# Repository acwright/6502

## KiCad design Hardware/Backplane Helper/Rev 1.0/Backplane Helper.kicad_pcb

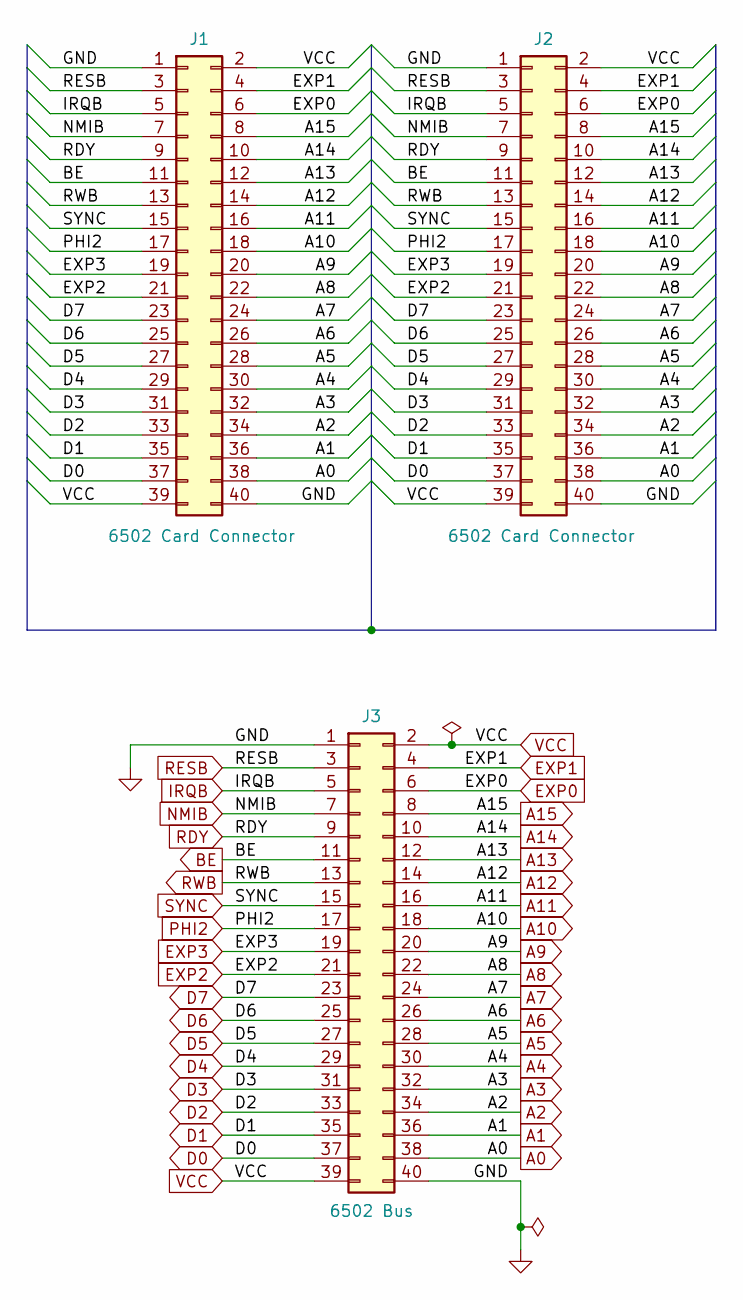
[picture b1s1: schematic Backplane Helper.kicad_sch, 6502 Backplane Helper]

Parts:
J1, J2: 6502 Card Connector; RHDR40W82P485X254_2X20_5740X93; Mouser 571-5-5530843-4
J3: 6502 Bus; 6502 Bus Connector; Digikey 732-5401-ND

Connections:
A0: J1.38, J2.38, J3.38
A1: J1.36, J2.36, J3.36
A2: J1.34, J2.34, J3.34
A3: J1.32, J2.32, J3.32
A4: J1.30, J2.30, J3.30
A5: J1.28, J2.28, J3.28
A6: J1.26, J2.26, J3.26
A7: J1.24, J2.24, J3.24
A8: J1.22, J2.22, J3.22
A9: J1.20, J2.20, J3.20
A10: J1.18, J2.18, J3.18
A11: J1.16, J2.16, J3.16
A12: J1.14, J2.14, J3.14
A13: J1.12, J2.12, J3.12
A14: J1.10, J2.10, J3.10
A15: J1.8, J2.8, J3.8
BE: J1.11, J2.11, J3.11
D0: J1.37, J2.37, J3.37
D1: J1.35, J2.35, J3.35
D2: J1.33, J2.33, J3.33
D3: J1.31, J2.31, J3.31
D4: J1.29, J2.29, J3.29
D5: J1.27, J2.27, J3.27
D6: J1.25, J2.25, J3.25
D7: J1.23, J2.23, J3.23
EXP0: J1.6, J2.6, J3.6
EXP1: J1.4, J2.4, J3.4
EXP2: J1.21, J2.21, J3.21
EXP3: J1.19, J2.19, J3.19
GND: J1.1, J1.40, J2.1, J2.40, J3.1, J3.40
IRQB: J1.5, J2.5, J3.5
NMIB: J1.7, J2.7, J3.7
PHI2: J1.17, J2.17, J3.17
RDY: J1.9, J2.9, J3.9
RESB: J1.3, J2.3, J3.3
RWB: J1.13, J2.13, J3.13
SYNC: J1.15, J2.15, J3.15
VCC: J1.2, J1.39, J2.2, J2.39, J3.2, J3.39

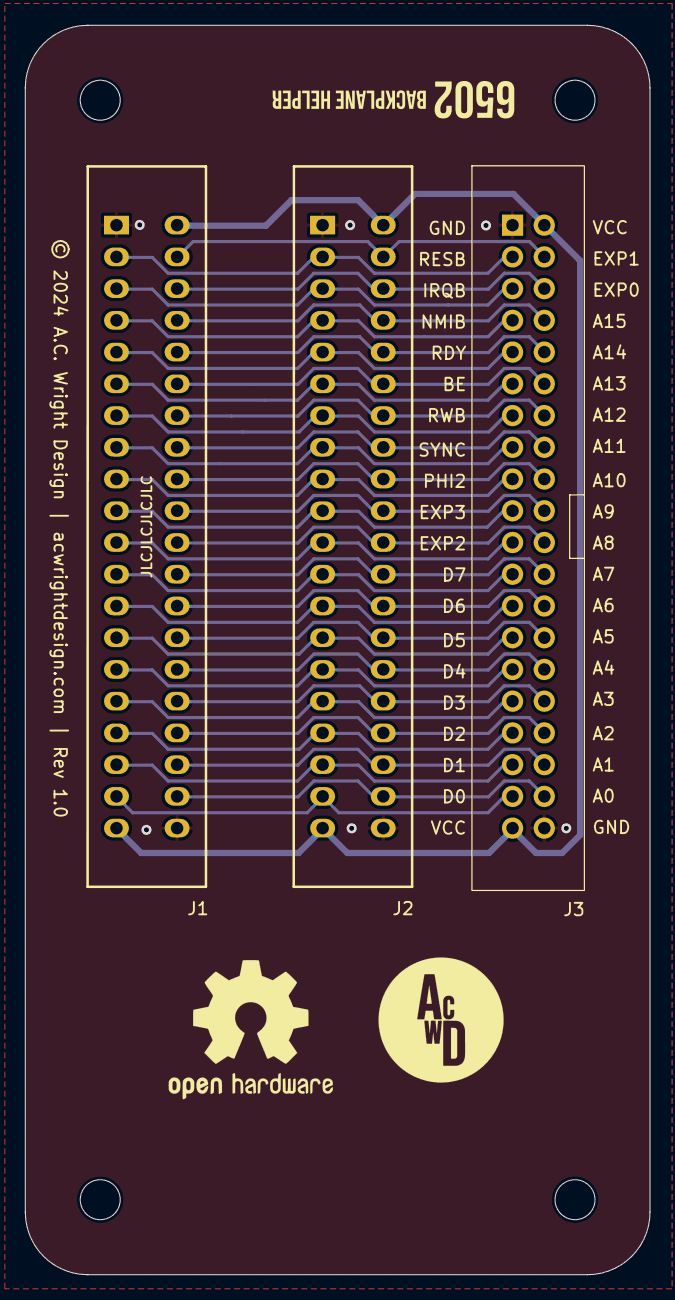
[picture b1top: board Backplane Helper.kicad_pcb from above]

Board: 2 copper layers, 50.0 x 100.0 mm, 7 parts (0 on the bottom side), 38 nets.

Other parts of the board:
H1, H2, H3, H4: MountingHole; MountingHole_3.2mm_M3

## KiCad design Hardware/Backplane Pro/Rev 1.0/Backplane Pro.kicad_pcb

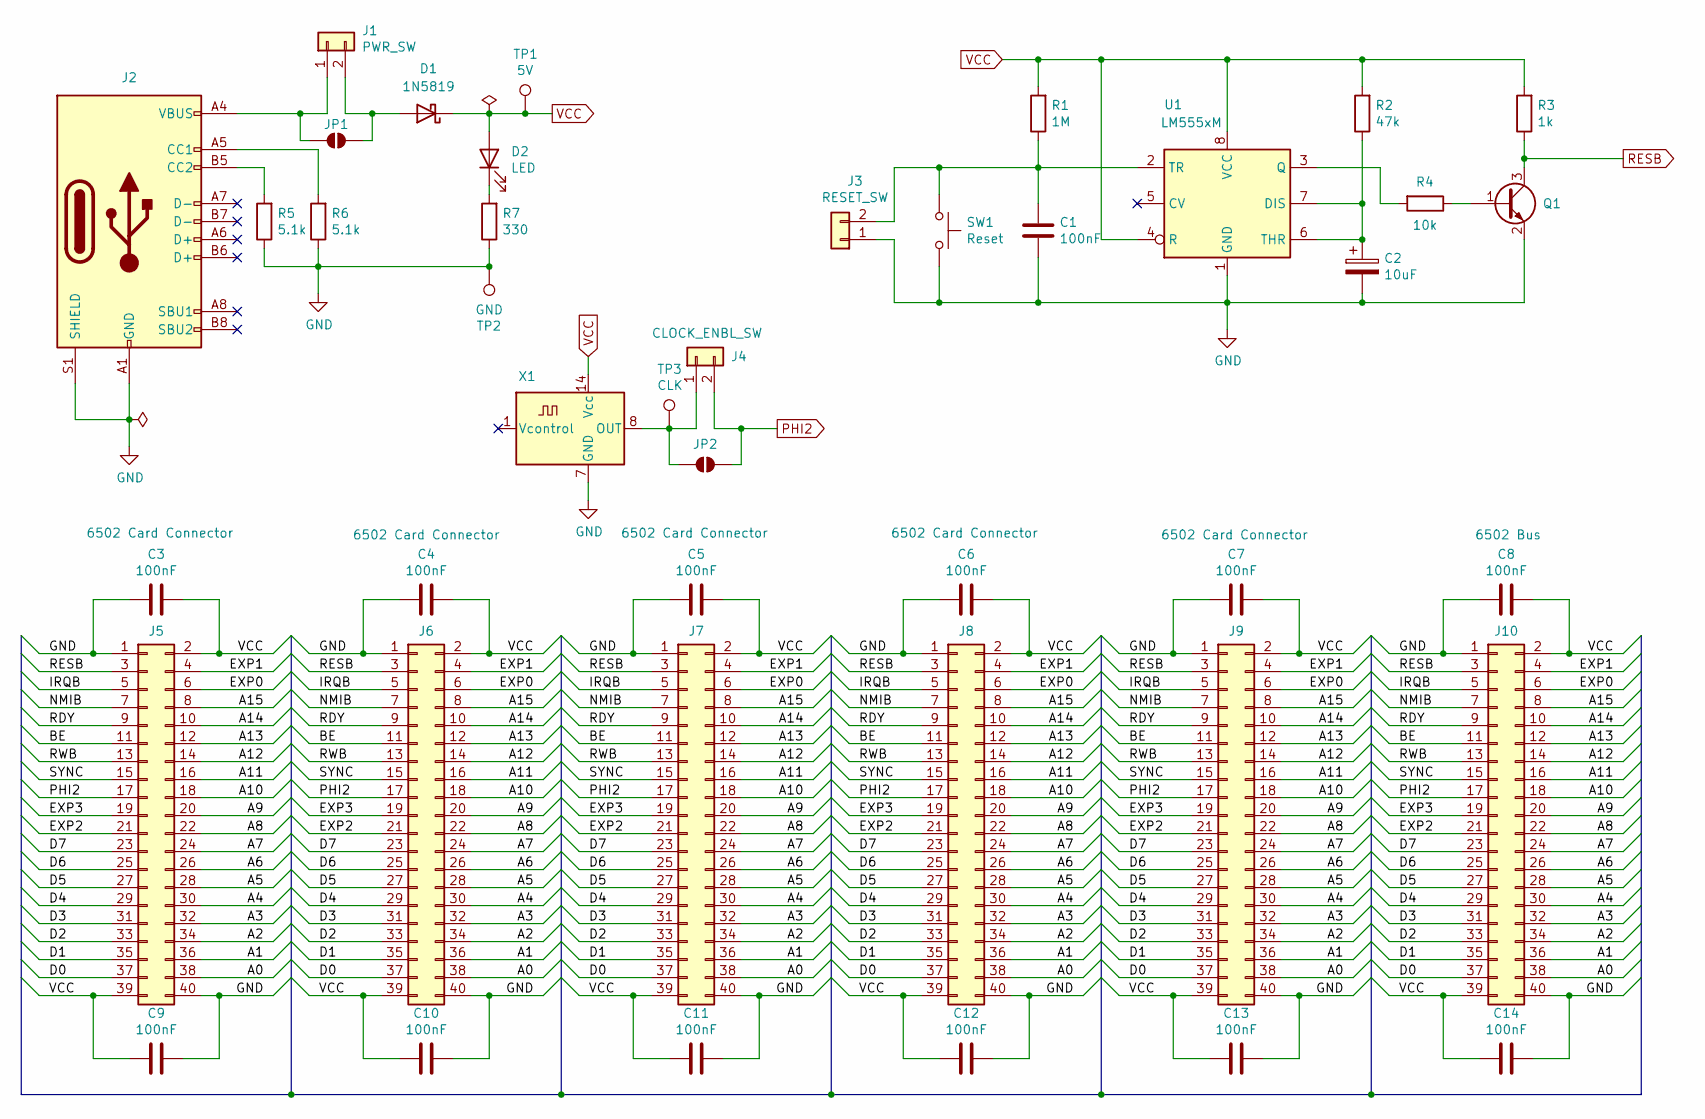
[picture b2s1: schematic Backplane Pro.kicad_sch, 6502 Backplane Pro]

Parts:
C1, C3, C4, C5, C6, C7, C8, C9, C10, C11, C12, C13, C14: 100nF; C_0805_2012Metric; LCSC C49678
C2: 10uF; C_1206_3216Metric; LCSC C7171
D1: 1N5819; D_SOD-323F; LCSC C191023
D2: LED; LED_0805_2012Metric; LCSC C2297
J1: PWR_SW; JST_XH_B2B-XH-A_1x02_P2.50mm_Vertical; Digikey 455-2247-ND
J2: USB_C_Receptacle_USB2.0; USB_C_Receptacle_HRO_TYPE-C-31-M-12; LCSC C2988369
J3: RESET_SW; JST_XH_B2B-XH-A_1x02_P2.50mm_Vertical; Digikey 455-2247-ND
J4: CLOCK_ENBL_SW; JST_XH_B2B-XH-A_1x02_P2.50mm_Vertical; Digikey 455-2247-ND
J5, J6, J7, J8, J9: 6502 Card Connector; RHDR40W82P485X254_2X20_5740X93; Mouser 571-5-5530843-4
J10: 6502 Bus; 6502 Bus Connector
JP1, JP2: SolderJumper_2_Open; SolderJumper-2_P1.3mm_Open_RoundedPad1.0x1.5mm
Q1: Q_NPN_BEC; SOT-23; LCSC C2150
R1: 1M; R_0805_2012Metric; LCSC C17514
R2: 47k; R_0805_2012Metric; LCSC C17713
R3: 1k; R_0805_2012Metric; LCSC C17513
R4: 10k; R_0805_2012Metric; LCSC C17414
R5, R6: 5.1k; R_0805_2012Metric; LCSC C27834
R7: 330; R_0805_2012Metric; LCSC C17630
SW1: Reset; SW_TS-1187A-B-A-B; LCSC C318884
TP1: 5V; TestPoint_Pad_1.0x1.0mm
TP2: GND; TestPoint_Pad_1.0x1.0mm
TP3: CLK; TestPoint_Pad_1.0x1.0mm
U1: LM555xM; SOIC-8_3.9x4.9mm_P1.27mm; LCSC C7593
X1: OCXO-14; Oscillator_DIP-14

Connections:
/A0: J5.38, J6.38, J7.38, J8.38, J9.38, J10.38
/A1: J5.36, J6.36, J7.36, J8.36, J9.36, J10.36
/A2: J5.34, J6.34, J7.34, J8.34, J9.34, J10.34
/A3: J5.32, J6.32, J7.32, J8.32, J9.32, J10.32
/A4: J5.30, J6.30, J7.30, J8.30, J9.30, J10.30
/A5: J5.28, J6.28, J7.28, J8.28, J9.28, J10.28
/A6: J5.26, J6.26, J7.26, J8.26, J9.26, J10.26
/A7: J5.24, J6.24, J7.24, J8.24, J9.24, J10.24
/A8: J5.22, J6.22, J7.22, J8.22, J9.22, J10.22
/A9: J5.20, J6.20, J7.20, J8.20, J9.20, J10.20
/A10: J5.18, J6.18, J7.18, J8.18, J9.18, J10.18
/A11: J5.16, J6.16, J7.16, J8.16, J9.16, J10.16
/A12: J5.14, J6.14, J7.14, J8.14, J9.14, J10.14
/A13: J5.12, J6.12, J7.12, J8.12, J9.12, J10.12
/A14: J5.10, J6.10, J7.10, J8.10, J9.10, J10.10
/A15: J5.8, J6.8, J7.8, J8.8, J9.8, J10.8
/BE: J5.11, J6.11, J7.11, J8.11, J9.11, J10.11
/D0: J5.37, J6.37, J7.37, J8.37, J9.37, J10.37
/D1: J5.35, J6.35, J7.35, J8.35, J9.35, J10.35
/D2: J5.33, J6.33, J7.33, J8.33, J9.33, J10.33
/D3: J5.31, J6.31, J7.31, J8.31, J9.31, J10.31
/D4: J5.29, J6.29, J7.29, J8.29, J9.29, J10.29
/D5: J5.27, J6.27, J7.27, J8.27, J9.27, J10.27
/D6: J5.25, J6.25, J7.25, J8.25, J9.25, J10.25
/D7: J5.23, J6.23, J7.23, J8.23, J9.23, J10.23
/EXP0: J5.6, J6.6, J7.6, J8.6, J9.6, J10.6
/EXP1: J5.4, J6.4, J7.4, J8.4, J9.4, J10.4
/EXP2: J5.21, J6.21, J7.21, J8.21, J9.21, J10.21
/EXP3: J5.19, J6.19, J7.19, J8.19, J9.19, J10.19
/IRQB: J5.5, J6.5, J7.5, J8.5, J9.5, J10.5
/NMIB: J5.7, J6.7, J7.7, J8.7, J9.7, J10.7
/RDY: J5.9, J6.9, J7.9, J8.9, J9.9, J10.9
/RWB: J5.13, J6.13, J7.13, J8.13, J9.13, J10.13
/SYNC: J5.15, J6.15, J7.15, J8.15, J9.15, J10.15
GND: C1.2, C2.2, C3.2, C4.2, C5.2, C6.2, C7.2, C8.2, C9.1, C10.1, C11.1, C12.1, C13.1, C14.1, J2.A1 (GND), J2.A12 (GND), J2.B1 (GND), J2.B12 (GND), J2.S1 (SHIELD), J3.1, J5.1, J5.40, J6.1, J6.40, J7.1, J7.40, J8.1, J8.40, J9.1, J9.40, J10.1, J10.40, Q1.2 (E), R5.1, R6.1, R7.1, SW1.2, TP2.1, U1.1 (GND), X1.7 (GND)
unnamed: D1.2 (A), J1.2, JP1.2 (B)
unnamed: D2.1 (K), R7.2
unnamed: J1.1, J2.A4 (VBUS), J2.A9 (VBUS), J2.B4 (VBUS), J2.B9 (VBUS), JP1.1 (A)
unnamed: J2.A5 (CC1), R6.2
unnamed: J2.B5 (CC2), R5.2
unnamed: C1.1, J3.2, R1.1, SW1.1, U1.2 (TR)
unnamed: J4.1, JP2.1 (A), TP3.1, X1.8 (OUT)
unnamed: Q1.1 (B), R4.1
unnamed: C2.1, R2.1, U1.6 (THR), U1.7 (DIS)
unnamed: R4.2, U1.3 (Q)
PHI2: J4.2, J5.17, J6.17, J7.17, J8.17, J9.17, J10.17, JP2.2 (B)
RESB: J5.3, J6.3, J7.3, J8.3, J9.3, J10.3, Q1.3 (C), R3.1
VCC: C3.1, C4.1, C5.1, C6.1, C7.1, C8.1, C9.2, C10.2, C11.2, C12.2, C13.2, C14.2, D1.1 (K), D2.2 (A), J5.2, J5.39, J6.2, J6.39, J7.2, J7.39, J8.2, J8.39, J9.2, J9.39, J10.2, J10.39, R1.2, R2.2, R3.2, TP1.1, U1.4 (R), U1.8 (VCC), X1.14 (Vcc)

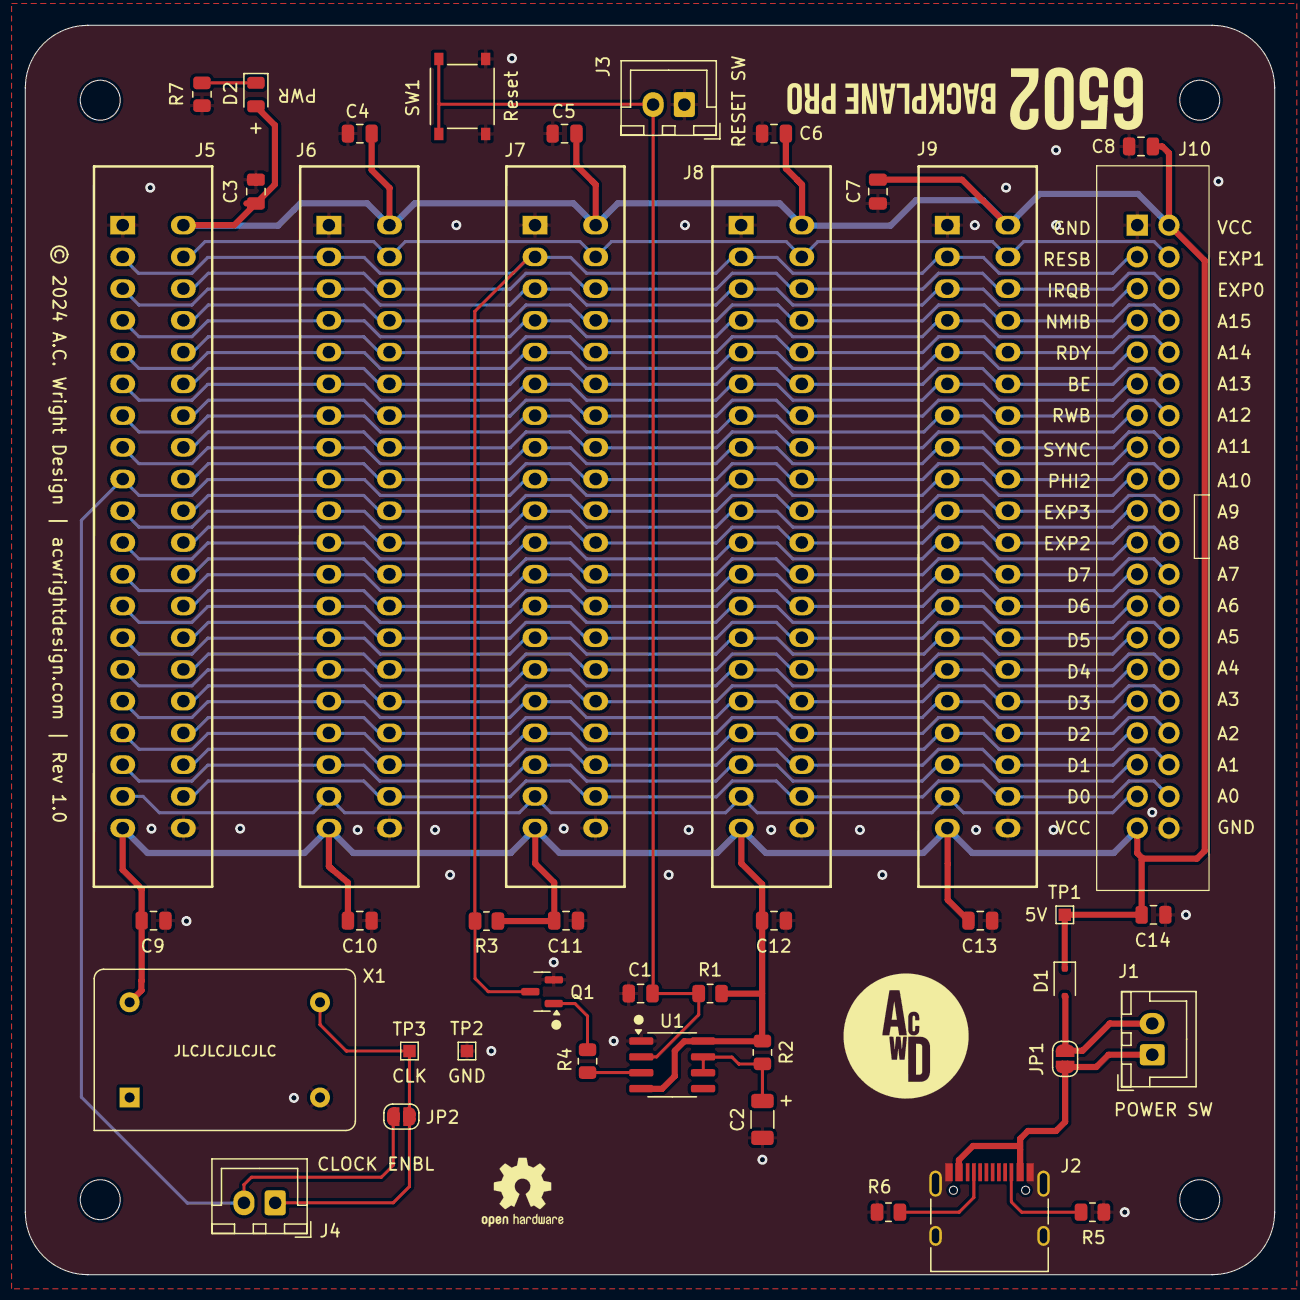
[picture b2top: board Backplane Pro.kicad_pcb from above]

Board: 2 copper layers, 100.0 x 100.0 mm, 46 parts (0 on the bottom side), 48 nets.

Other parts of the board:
H1, H2, H3, H4: MountingHole; MountingHole_3.2mm_M3

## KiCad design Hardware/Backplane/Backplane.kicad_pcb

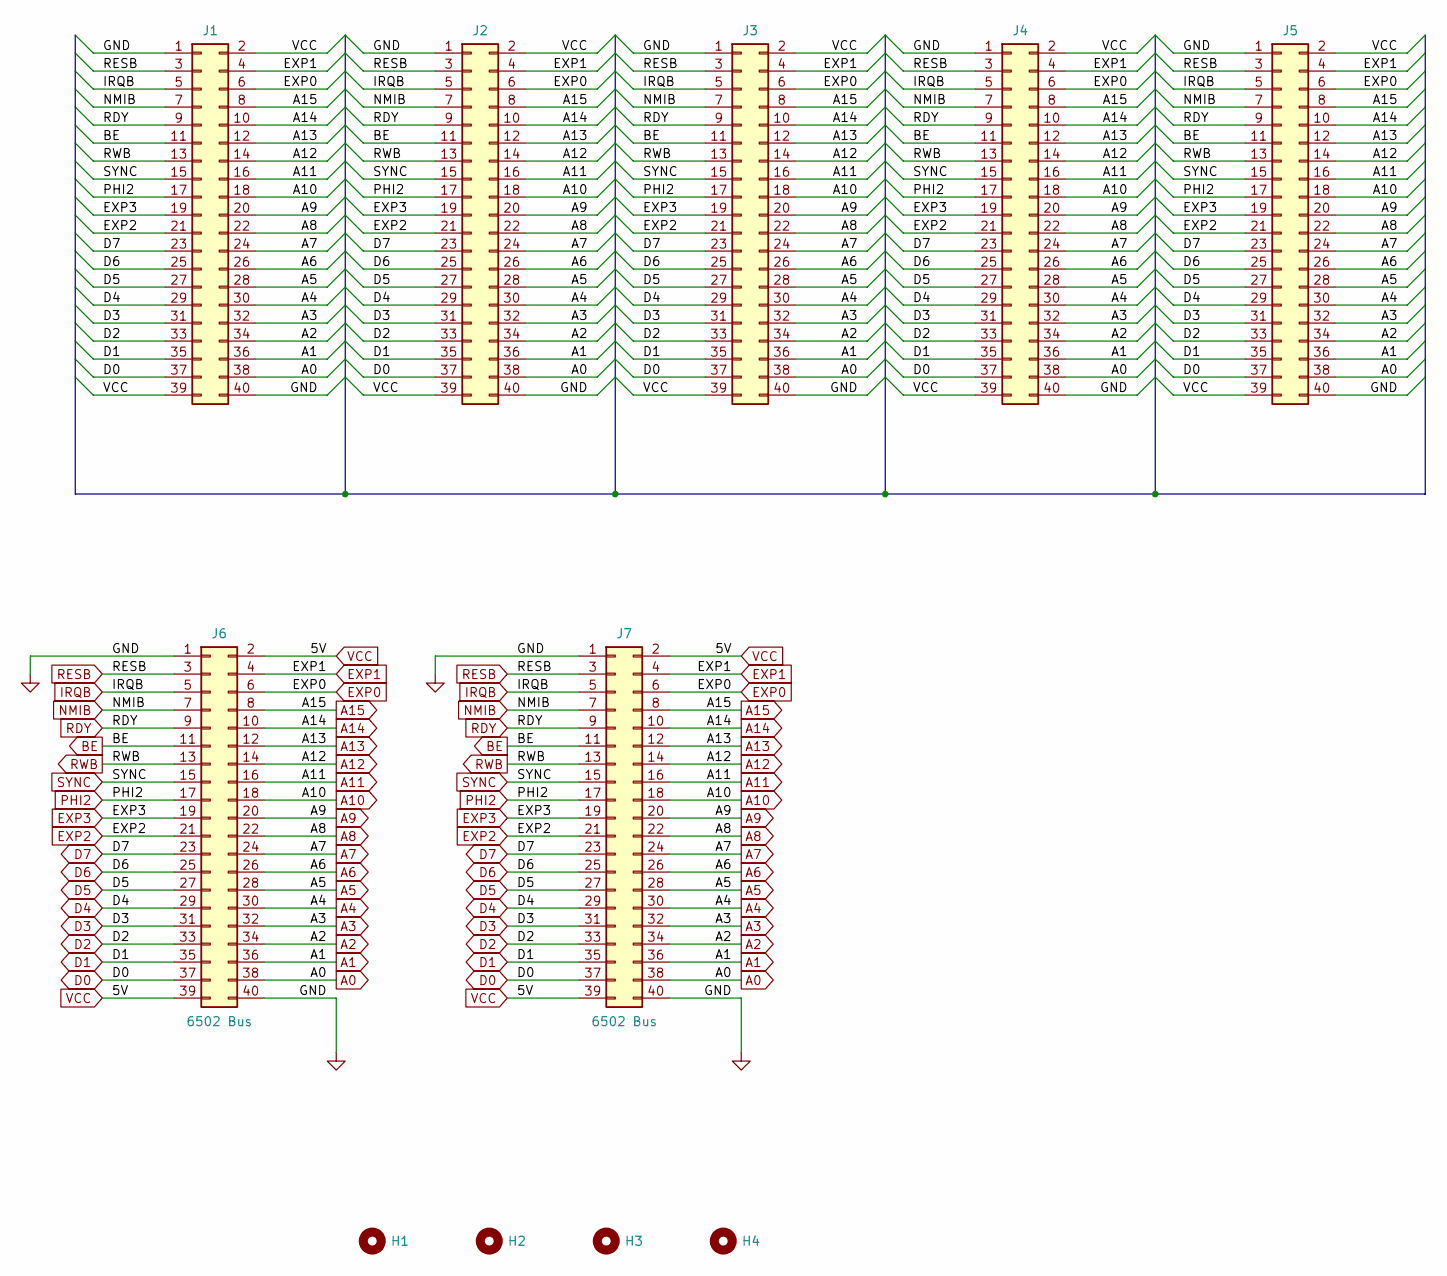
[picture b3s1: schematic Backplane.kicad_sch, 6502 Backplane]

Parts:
H1, H2, H3, H4: MountingHole; MountingHole_3.2mm_M3
J1, J2, J3, J4, J5: Conn_02x20_Odd_Even; RHDR40W82P485X254_2X20_5740X93; Mouser 571-5-5530843-4
J6, J7: 6502 Bus; 6502 Bus Connector

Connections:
A0: J1.38, J2.38, J3.38, J4.38, J5.38, J6.38, J7.38
A1: J1.36, J2.36, J3.36, J4.36, J5.36, J6.36, J7.36
A2: J1.34, J2.34, J3.34, J4.34, J5.34, J6.34, J7.34
A3: J1.32, J2.32, J3.32, J4.32, J5.32, J6.32, J7.32
A4: J1.30, J2.30, J3.30, J4.30, J5.30, J6.30, J7.30
A5: J1.28, J2.28, J3.28, J4.28, J5.28, J6.28, J7.28
A6: J1.26, J2.26, J3.26, J4.26, J5.26, J6.26, J7.26
A7: J1.24, J2.24, J3.24, J4.24, J5.24, J6.24, J7.24
A8: J1.22, J2.22, J3.22, J4.22, J5.22, J6.22, J7.22
A9: J1.20, J2.20, J3.20, J4.20, J5.20, J6.20, J7.20
A10: J1.18, J2.18, J3.18, J4.18, J5.18, J6.18, J7.18
A11: J1.16, J2.16, J3.16, J4.16, J5.16, J6.16, J7.16
A12: J1.14, J2.14, J3.14, J4.14, J5.14, J6.14, J7.14
A13: J1.12, J2.12, J3.12, J4.12, J5.12, J6.12, J7.12
A14: J1.10, J2.10, J3.10, J4.10, J5.10, J6.10, J7.10
A15: J1.8, J2.8, J3.8, J4.8, J5.8, J6.8, J7.8
BE: J1.11, J2.11, J3.11, J4.11, J5.11, J6.11, J7.11
D0: J1.37, J2.37, J3.37, J4.37, J5.37, J6.37, J7.37
D1: J1.35, J2.35, J3.35, J4.35, J5.35, J6.35, J7.35
D2: J1.33, J2.33, J3.33, J4.33, J5.33, J6.33, J7.33
D3: J1.31, J2.31, J3.31, J4.31, J5.31, J6.31, J7.31
D4: J1.29, J2.29, J3.29, J4.29, J5.29, J6.29, J7.29
D5: J1.27, J2.27, J3.27, J4.27, J5.27, J6.27, J7.27
D6: J1.25, J2.25, J3.25, J4.25, J5.25, J6.25, J7.25
D7: J1.23, J2.23, J3.23, J4.23, J5.23, J6.23, J7.23
EXP0: J1.6, J2.6, J3.6, J4.6, J5.6, J6.6, J7.6
EXP1: J1.4, J2.4, J3.4, J4.4, J5.4, J6.4, J7.4
EXP2: J1.21, J2.21, J3.21, J4.21, J5.21, J6.21, J7.21
EXP3: J1.19, J2.19, J3.19, J4.19, J5.19, J6.19, J7.19
GND: J1.1, J1.40, J2.1, J2.40, J3.1, J3.40, J4.1, J4.40, J5.1, J5.40, J6.1, J6.40, J7.1, J7.40
IRQB: J1.5, J2.5, J3.5, J4.5, J5.5, J6.5, J7.5
NMIB: J1.7, J2.7, J3.7, J4.7, J5.7, J6.7, J7.7
PHI2: J1.17, J2.17, J3.17, J4.17, J5.17, J6.17, J7.17
RDY: J1.9, J2.9, J3.9, J4.9, J5.9, J6.9, J7.9
RESB: J1.3, J2.3, J3.3, J4.3, J5.3, J6.3, J7.3
RWB: J1.13, J2.13, J3.13, J4.13, J5.13, J6.13, J7.13
SYNC: J1.15, J2.15, J3.15, J4.15, J5.15, J6.15, J7.15
VCC: J1.2, J1.39, J2.2, J2.39, J3.2, J3.39, J4.2, J4.39, J5.2, J5.39, J6.2, J6.39, J7.2, J7.39

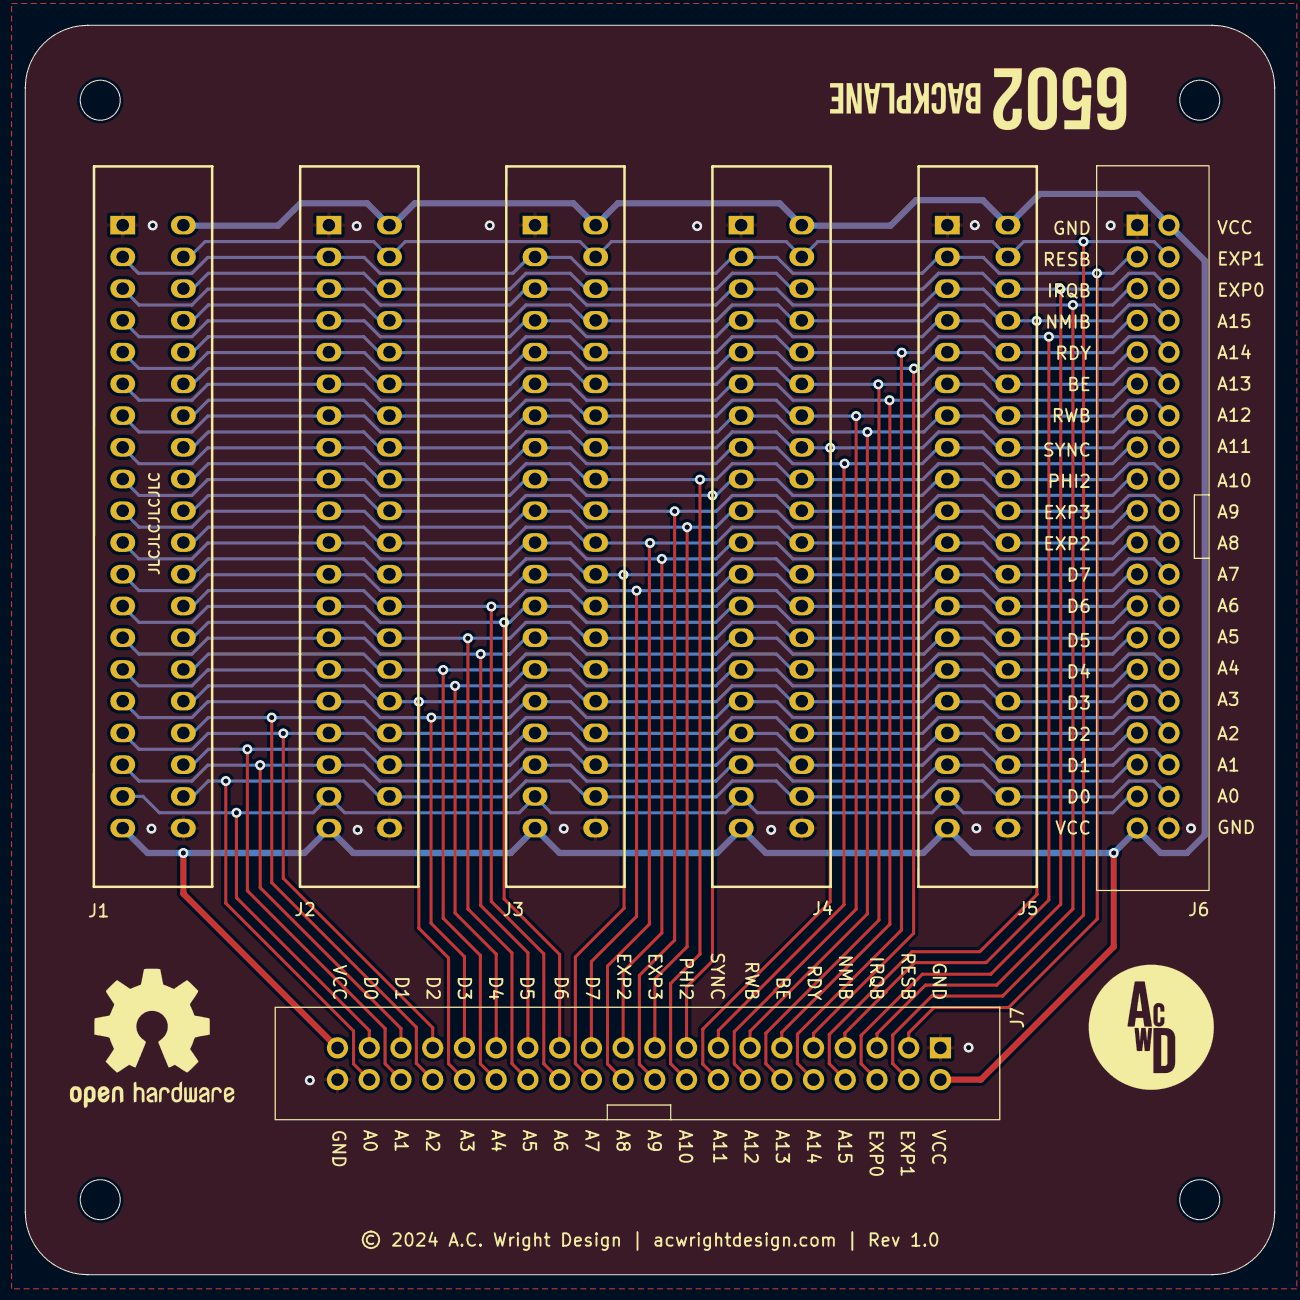
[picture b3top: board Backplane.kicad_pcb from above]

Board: 2 copper layers, 100.0 x 100.0 mm, 11 parts (0 on the bottom side), 38 nets.

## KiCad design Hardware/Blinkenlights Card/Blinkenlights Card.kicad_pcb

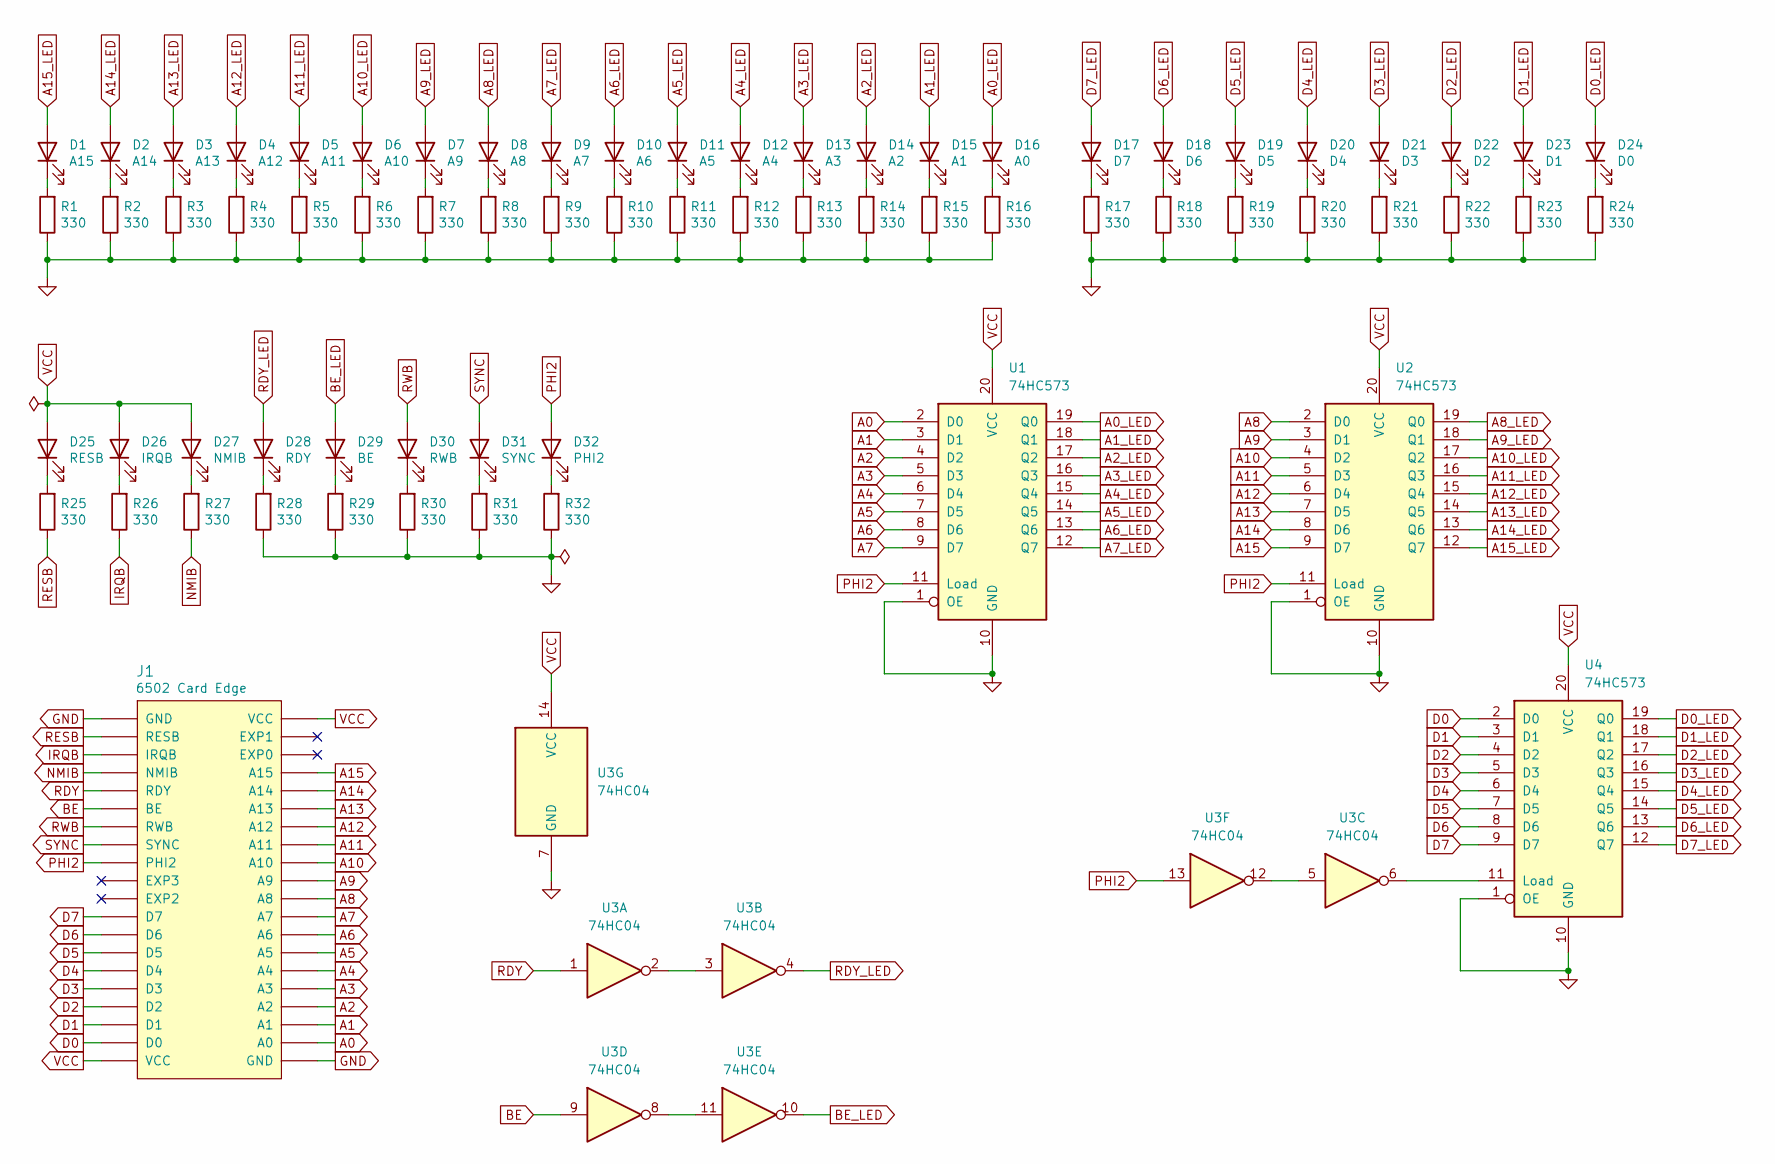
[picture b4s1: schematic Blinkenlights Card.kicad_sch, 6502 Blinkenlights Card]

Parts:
D1: A15; LED_0805_2012Metric; LCSC C2297
D2: A14; LED_0805_2012Metric; LCSC C2297
D3: A13; LED_0805_2012Metric; LCSC C2297
D4: A12; LED_0805_2012Metric; LCSC C2297
D5: A11; LED_0805_2012Metric; LCSC C2297
D6: A10; LED_0805_2012Metric; LCSC C2297
D7: A9; LED_0805_2012Metric; LCSC C2297
D8: A8; LED_0805_2012Metric; LCSC C2297
D9: A7; LED_0805_2012Metric; LCSC C2297
D10: A6; LED_0805_2012Metric; LCSC C2297
D11: A5; LED_0805_2012Metric; LCSC C2297
D12: A4; LED_0805_2012Metric; LCSC C2297
D13: A3; LED_0805_2012Metric; LCSC C2297
D14: A2; LED_0805_2012Metric; LCSC C2297
D15: A1; LED_0805_2012Metric; LCSC C2297
D16: A0; LED_0805_2012Metric; LCSC C2297
D17: D7; LED_0805_2012Metric; LCSC C2297
D18: D6; LED_0805_2012Metric; LCSC C2297
D19: D5; LED_0805_2012Metric; LCSC C2297
D20: D4; LED_0805_2012Metric; LCSC C2297
D21: D3; LED_0805_2012Metric; LCSC C2297
D22: D2; LED_0805_2012Metric; LCSC C2297
D23: D1; LED_0805_2012Metric; LCSC C2297
D24: D0; LED_0805_2012Metric; LCSC C2297
D25: RESB; LED_0805_2012Metric; LCSC C2297
D26: IRQB; LED_0805_2012Metric; LCSC C2295
D27: NMIB; LED_0805_2012Metric; LCSC C2295
D28: RDY; LED_0805_2012Metric; LCSC C2296
D29: BE; LED_0805_2012Metric; LCSC C2296
D30: RWB; LED_0805_2012Metric; LCSC C2296
D31: SYNC; LED_0805_2012Metric; LCSC C2293
D32: PHI2; LED_0805_2012Metric; LCSC C2293
J1: 6502 Card Edge
R1, R2, R3, R4, R5, R6, R7, R8, R9, R10, R11, R12, R13, R14, R15, R16, R17, R18, R19, R20, R21, R22, R23, R24, R25, R26, R27, R28, R29, R30, R31, R32: 330; R_0805_2012Metric; LCSC C17630
U1, U2, U4: 74HC573; SOIC-20W_7.5x12.8mm_P1.27mm; LCSC C5608
U3: 74HC04; SOIC-14_3.9x8.7mm_P1.27mm; LCSC C5590

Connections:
A0: J1.A0, U1.2 (D0)
A0_LED: D16.2 (A), U1.19 (Q0)
A1: J1.A1, U1.3 (D1)
A1_LED: D15.2 (A), U1.18 (Q1)
A2: J1.A2, U1.4 (D2)
A2_LED: D14.2 (A), U1.17 (Q2)
A3: J1.A3, U1.5 (D3)
A3_LED: D13.2 (A), U1.16 (Q3)
A4: J1.A4, U1.6 (D4)
A4_LED: D12.2 (A), U1.15 (Q4)
A5: J1.A5, U1.7 (D5)
A5_LED: D11.2 (A), U1.14 (Q5)
A6: J1.A6, U1.8 (D6)
A6_LED: D10.2 (A), U1.13 (Q6)
A7: J1.A7, U1.9 (D7)
A7_LED: D9.2 (A), U1.12 (Q7)
A8: J1.A8, U2.2 (D0)
A8_LED: D8.2 (A), U2.19 (Q0)
A9: J1.A9, U2.3 (D1)
A9_LED: D7.2 (A), U2.18 (Q1)
A10: J1.A10, U2.4 (D2)
A10_LED: D6.2 (A), U2.17 (Q2)
A11: J1.A11, U2.5 (D3)
A11_LED: D5.2 (A), U2.16 (Q3)
A12: J1.A12, U2.6 (D4)
A12_LED: D4.2 (A), U2.15 (Q4)
A13: J1.A13, U2.7 (D5)
A13_LED: D3.2 (A), U2.14 (Q5)
A14: J1.A14, U2.8 (D6)
A14_LED: D2.2 (A), U2.13 (Q6)
A15: J1.A15, U2.9 (D7)
A15_LED: D1.2 (A), U2.12 (Q7)
BE: J1.BE, U3.9
BE_LED: D29.2 (A), U3.10
D0: J1.D0, U4.2 (D0)
D0_LED: D24.2 (A), U4.19 (Q0)
D1: J1.D1, U4.3 (D1)
D1_LED: D23.2 (A), U4.18 (Q1)
D2: J1.D2, U4.4 (D2)
D2_LED: D22.2 (A), U4.17 (Q2)
D3: J1.D3, U4.5 (D3)
D3_LED: D21.2 (A), U4.16 (Q3)
D4: J1.D4, U4.6 (D4)
D4_LED: D20.2 (A), U4.15 (Q4)
D5: J1.D5, U4.7 (D5)
D5_LED: D19.2 (A), U4.14 (Q5)
D6: J1.D6, U4.8 (D6)
D6_LED: D18.2 (A), U4.13 (Q6)
D7: J1.D7, U4.9 (D7)
D7_LED: D17.2 (A), U4.12 (Q7)
GND: J1.GND, R1.1, R2.1, R3.1, R4.1, R5.1, R6.1, R7.1, R8.1, R9.1, R10.1, R11.1, R12.1, R13.1, R14.1, R15.1, R16.1, R17.1, R18.1, R19.1, R20.1, R21.1, R22.1, R23.1, R24.1, R28.1, R29.1, R30.1, R31.1, R32.1, U1.1 (OE), U1.10 (GND), U2.1 (OE), U2.10 (GND), U3.7 (GND), U4.1 (OE), U4.10 (GND)
IRQB: J1.IRQB, R26.1
NMIB: J1.NMIB, R27.1
unnamed: D1.1 (K), R1.2
unnamed: D2.1 (K), R2.2
unnamed: D3.1 (K), R3.2
unnamed: D4.1 (K), R4.2
unnamed: D5.1 (K), R5.2
unnamed: D6.1 (K), R6.2
unnamed: D7.1 (K), R7.2
unnamed: D8.1 (K), R8.2
unnamed: D9.1 (K), R9.2
unnamed: D10.1 (K), R10.2
unnamed: D11.1 (K), R11.2
unnamed: D12.1 (K), R12.2
unnamed: D13.1 (K), R13.2
unnamed: D14.1 (K), R14.2
unnamed: D15.1 (K), R15.2
unnamed: D16.1 (K), R16.2
unnamed: D17.1 (K), R17.2
unnamed: D18.1 (K), R18.2
unnamed: D19.1 (K), R19.2
unnamed: D20.1 (K), R20.2
unnamed: D21.1 (K), R21.2
unnamed: D22.1 (K), R22.2
unnamed: D23.1 (K), R23.2
unnamed: D24.1 (K), R24.2
unnamed: D25.1 (K), R25.2
unnamed: D26.1 (K), R26.2
unnamed: D27.1 (K), R27.2
unnamed: D28.1 (K), R28.2
unnamed: D29.1 (K), R29.2
unnamed: D30.1 (K), R30.2
unnamed: D31.1 (K), R31.2
unnamed: D32.1 (K), R32.2
unnamed: U3.2, U3.3
unnamed: U3.8, U3.11
unnamed: U3.5, U3.12
unnamed: U3.6, U4.11 (Load)
PHI2: D32.2 (A), J1.PHI2, U1.11 (Load), U2.11 (Load), U3.13
RDY: J1.RDY, U3.1
RDY_LED: D28.2 (A), U3.4
RESB: J1.RESB, R25.1
RWB: D30.2 (A), J1.RWB
SYNC: D31.2 (A), J1.SYNC
VCC: D25.2 (A), D26.2 (A), D27.2 (A), J1.VCC, U1.20 (VCC), U2.20 (VCC), U3.14 (VCC), U4.20 (VCC)

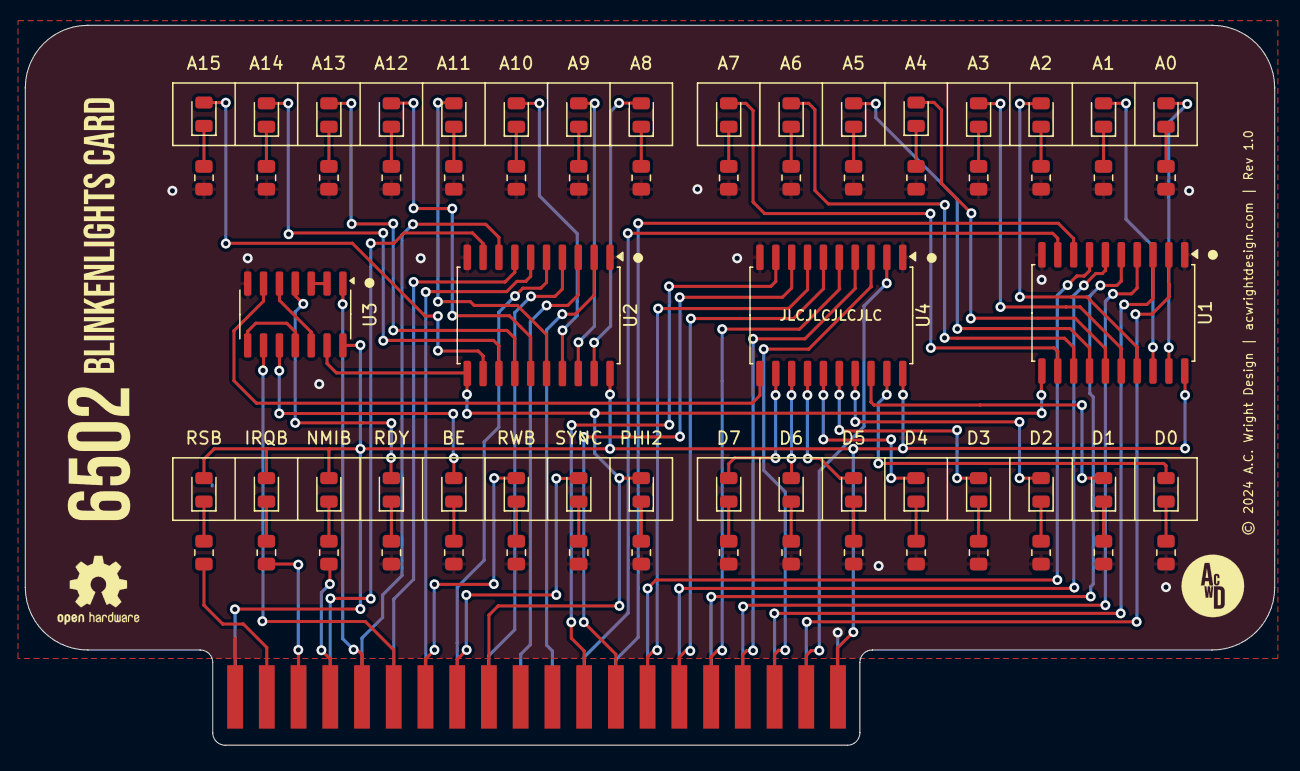
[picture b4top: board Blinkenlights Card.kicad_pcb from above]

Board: 2 copper layers, 100.0 x 57.6 mm, 69 parts (0 on the bottom side), 96 nets.

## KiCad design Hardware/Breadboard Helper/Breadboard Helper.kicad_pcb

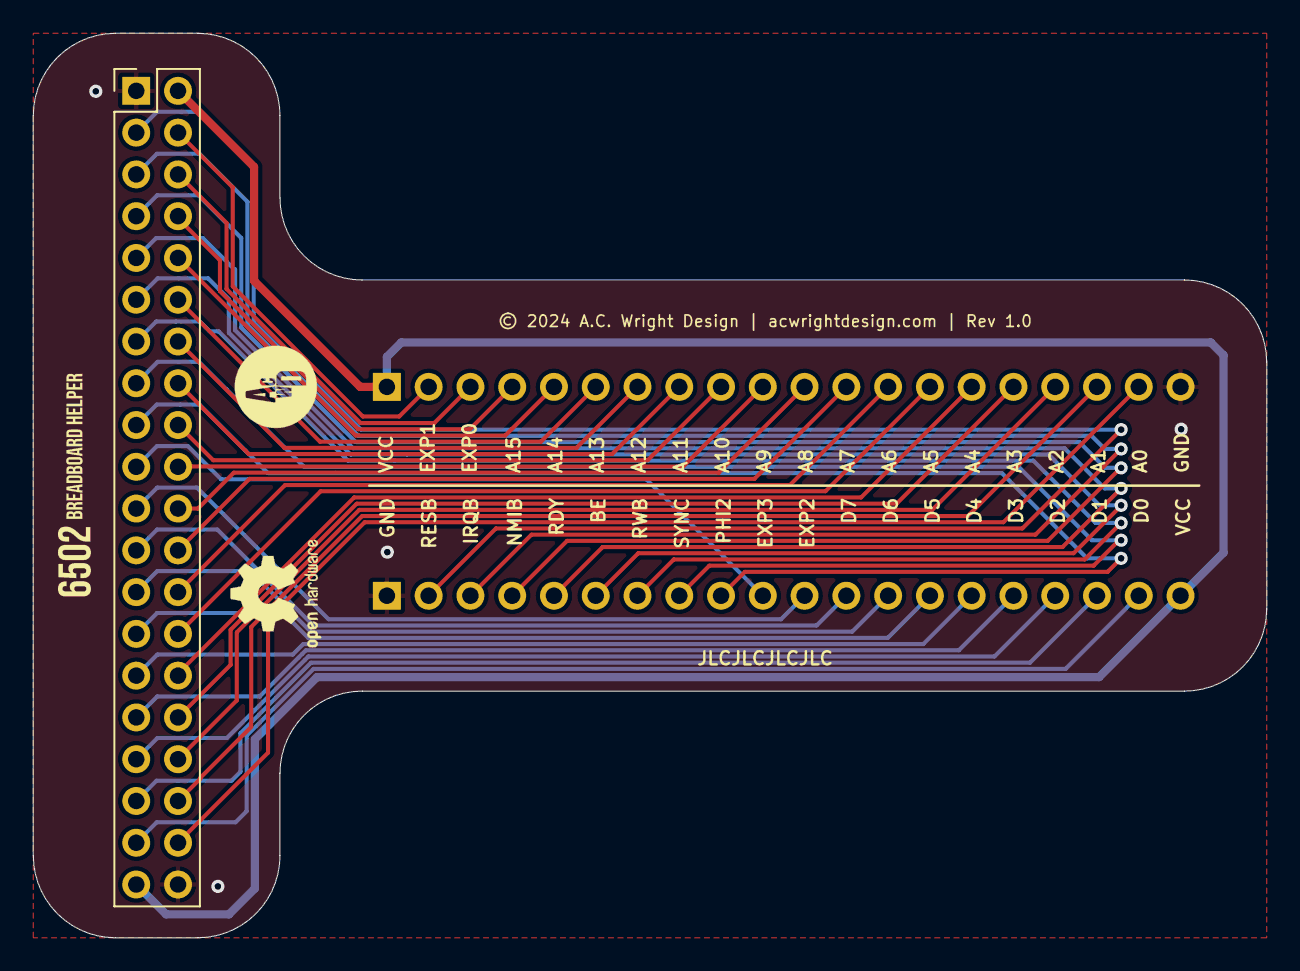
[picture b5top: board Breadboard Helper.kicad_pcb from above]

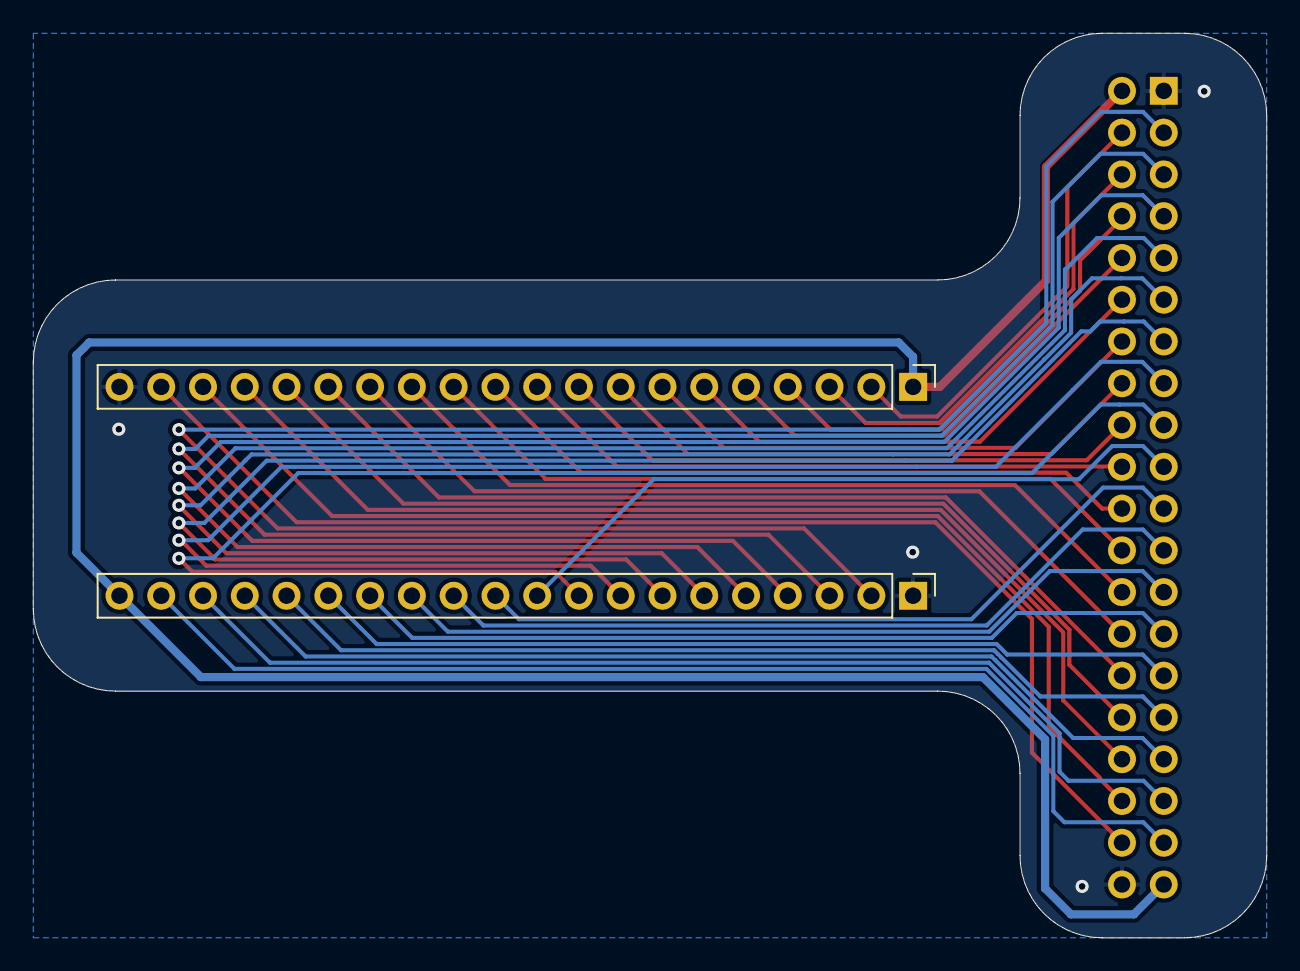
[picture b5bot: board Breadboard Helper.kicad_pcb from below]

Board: 2 copper layers, 75.0 x 55.0 mm, 3 parts (2 on the bottom side), 38 nets.

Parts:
J1: 6502 Bus; PinHeader_2x20_P2.54mm_Vertical
J2, J3: Conn_01x20; PinHeader_1x20_P2.54mm_Vertical

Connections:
A0: J1.38, J3.19
A1: J1.36, J3.18
A2: J1.34, J3.17
A3: J1.32, J3.16
A4: J1.30, J3.15
A5: J1.28, J3.14
A6: J1.26, J3.13
A7: J1.24, J3.12
A8: J1.22, J3.11
A9: J1.20, J3.10
A10: J1.18, J3.9
A11: J1.16, J3.8
A12: J1.14, J3.7
A13: J1.12, J3.6
A14: J1.10, J3.5
A15: J1.8, J3.4
BE: J1.11, J2.6
D0: J1.37, J2.19
D1: J1.35, J2.18
D2: J1.33, J2.17
D3: J1.31, J2.16
D4: J1.29, J2.15
D5: J1.27, J2.14
D6: J1.25, J2.13
D7: J1.23, J2.12
EXP0: J1.6, J3.3
EXP1: J1.4, J3.2
EXP2: J1.21, J2.11
EXP3: J1.19, J2.10
GND: J1.1, J1.40, J2.1, J3.20
IRQB: J1.5, J2.3
NMIB: J1.7, J2.4
PHI2: J1.17, J2.9
RDY: J1.9, J2.5
RESB: J1.3, J2.2
RWB: J1.13, J2.7
SYNC: J1.15, J2.8
VCC: J1.2, J1.39, J2.20, J3.1

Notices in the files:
Hardware/Backplane Helper/Rev 1.0/Backplane Helper.kicad_pcb:
© 2024 A.C. Wright Design | acwrightdesign.com | Rev 1.0
